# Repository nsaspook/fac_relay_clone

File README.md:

# fac_relay
Modified BLE software for the PIC24FV. Adds SPI and DFU-OTA firmware upgrades for the RN4020 module.

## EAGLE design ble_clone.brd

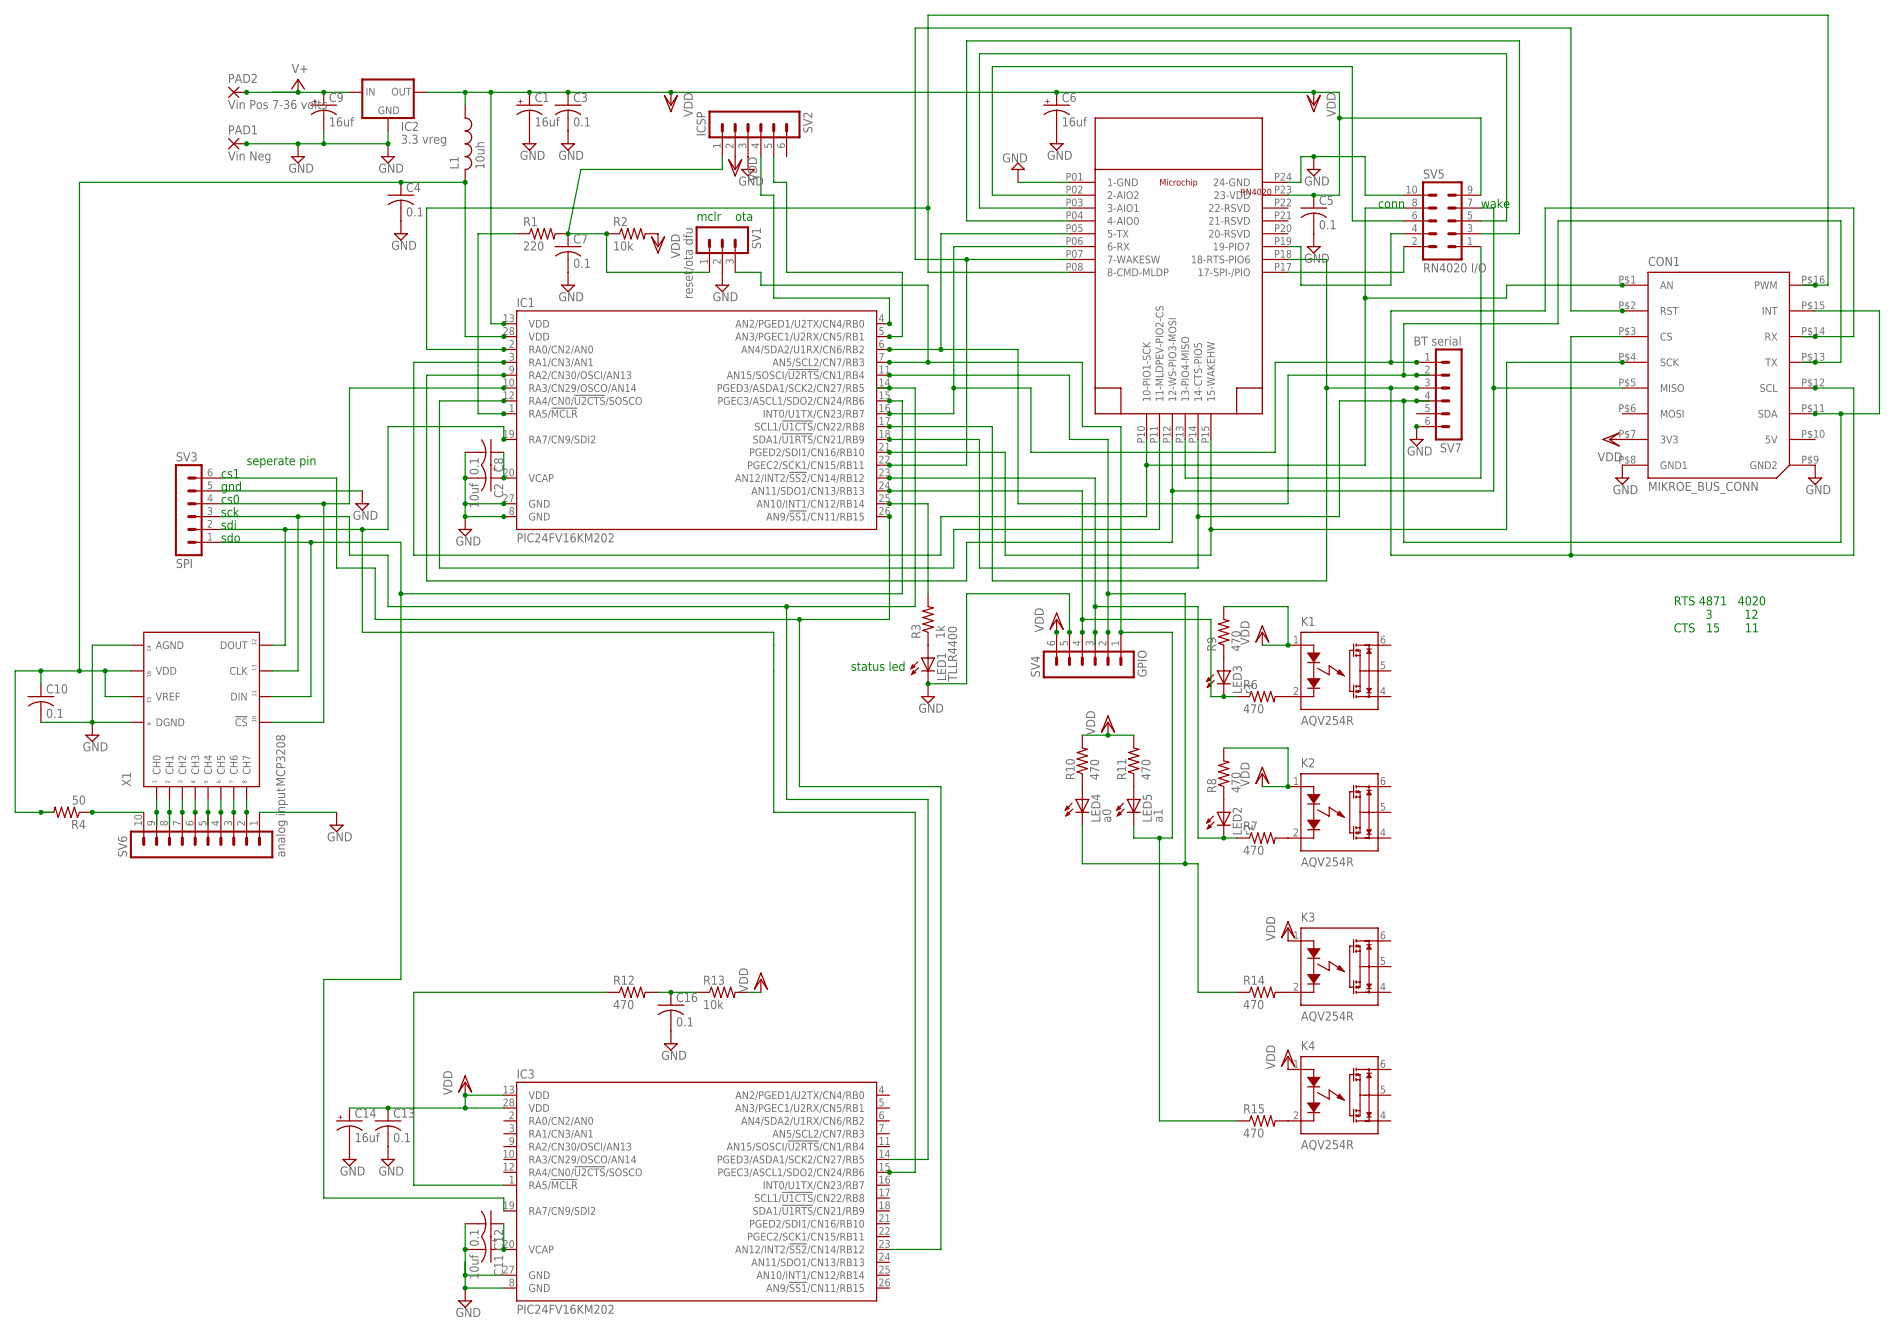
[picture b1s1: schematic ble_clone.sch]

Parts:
C1, C6, C9, C14: 16uf; TAP5-45
C2, C11: 10uf; TAP5-45
C3, C4, C5, C7, C8, C10: 0.1; C025-024X044
C12, C13, C16: 0.1; C0805
CON1: MIKROE_BUS_CONN; MIKROBUS_HOST_CONN
IC1, IC3: PIC24FV16KM202; DIL28-3
IC2: 3.3 vreg; 78XXL
K1, K2, K3, K4: AQV254R; DIL06
L1: 10uh; 0204/5
LED1: TLLR4400; LED3MM
LED2: r2; LED3MM
LED3: r1; LED3MM
LED4: a0; LED3MM
LED5: a1; LED3MM
PAD1: Vin Neg; 2,54/1,0
PAD2: Vin Pos 7-36 volts; 2,54/1,0
R1: 220; 0204V
R2, R13: 10k; 0204V
R3: 1k; 0204V
R4: 50; 0204V
R6, R7, R8, R9, R10, R11, R12, R14, R15: 470; 0204V
SV1: reset/ota dfu; MA03-1
SV2: ICSP; MA06-1
SV3: SPI; MA06-1
SV4: GPIO; MA06-1
SV5: RN4020 I/O; MA05-2
SV6: analog input; MA10-1
SV7: BT serial; MA06-1
U$1: RN4020; RN4020SMD
X1: MCP3208; DIP16

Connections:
GND: C1.-, C2.-, C3.2, C4.2, C5.2, C6.-, C7.2, C8.2, C9.-, C10.2, C11.-, C12.2, C13.2, C14.-, C16.2, CON1.P$8 (GND1), CON1.P$9 (GND2), IC1.8 (GND), IC1.27 (GND), IC2.GND, IC3.8 (GND), IC3.27 (GND), LED1.K (C), PAD1.1, SV1.2, SV2.3, SV3.5, SV4.5, SV5.10, SV6.1, SV7.6, U$1.P01 (1-GND), U$1.P24 (24-GND), X1.P$9 (DGND), X1.P$14 (AGND)
unnamed: CON1.P$16 (PWM), IC1.2 (RA0/CN2/AN0), U$1.P08 (8-CMD-MLDP)
unnamed: C7.1, R1.2, R2.1, SV1.1, SV2.1
unnamed: CON1.P$13 (TX), IC1.6 (AN4/SDA2/U1RX/CN6/RB2), SV7.2, U$1.P05 (5-TX)
unnamed: CON1.P$14 (RX), IC1.16 (INT0/U1TX/CN23/RB7), SV7.1, U$1.P06 (6-RX)
unnamed: CON1.P$2 (RST), IC1.22 (PGEC2/SCK1/CN15/RB11), U$1.P07 (7-WAKESW)
unnamed: IC1.1 (RA5/!MCLR), R1.1
unnamed: IC1.7 (AN5/SCL2/CN7/RB3), LED5.K (C), R15.1, SV1.3, SV4.1
unnamed: IC1.4 (AN2/PGED1/U2TX/CN4/RB0), SV2.4
unnamed: CON1.P$3 (CS), CON1.P$12 (SCL), IC1.17 (SCL1/!U1CTS!/CN22/RB8), SV7.3, U$1.P18 (18-RTS-PIO6)
unnamed: CON1.P$11 (SDA), CON1.P$15 (INT), IC1.18 (SDA1/!U1RTS!/CN21/RB9), SV7.4, U$1.P14 (14-CTS-PIO5)
unnamed: CON1.P$4 (SCK), IC1.21 (PGED2/SDI1/CN16/RB10), U$1.P15 (15-WAKEHW)
unnamed: CON1.P$5 (MISO), IC1.9 (RA2/CN30/OSCI/AN13), SV5.7, U$1.P12 (12-WS-PIO3-MOSI)
unnamed: CON1.P$1 (AN), IC1.3 (RA1/CN3/AN1), SV5.8, U$1.P10 (10-PIO1-SCK)
unnamed: IC1.12 (RA4/CN0/!U2CTS!/SOSCO), U$1.P11 (11-MLDPEV-PIO2-CS)
unnamed: IC1.5 (AN3/PGEC1/U2RX/CN5/RB1), SV2.5
unnamed: C4.1, C10.1, IC1.28 (VDD), L1.2, R4.2, X1.P$15 (VREF), X1.P$16 (VDD)
unnamed: C2.+, C8.1, IC1.20 (VCAP)
unnamed: IC1.10 (RA3/CN29/OSCO/AN14), SV3.4, X1.P$10 (!CS)
unnamed: IC1.19 (RA7/CN9/SDI2), IC3.15 (PGEC3/ASCL1/SDO2/CN24/RB6), SV3.2, X1.P$12 (DOUT)
unnamed: IC1.15 (PGEC3/ASCL1/SDO2/CN24/RB6), IC3.19 (RA7/CN9/SDI2), SV3.1, X1.P$11 (DIN)
unnamed: IC1.14 (PGED3/ASDA1/SCK2/CN27/RB5), IC3.14 (PGED3/ASDA1/SCK2/CN27/RB5), SV3.3, X1.P$13 (CLK)
unnamed: IC1.25 (AN10/INT1/CN12/RB14), R3.2
unnamed: IC1.26 (AN9/!SS1!/CN11/RB15), IC3.23 (AN12/INT2/!SS2!/CN14/RB12), SV3.6
unnamed: IC1.11 (AN15/SOSCI/!U2RTS!/CN1/RB4), LED4.K (C), R14.1, SV4.2
unnamed: IC1.23 (AN12/INT2/!SS2!/CN14/RB12), LED2.K (C), R7.1, SV4.3
unnamed: IC1.24 (AN11/SDO1/CN13/RB13), LED3.K (C), R6.1, SV4.4
unnamed: LED1.A, R3.1
unnamed: SV5.1, U$1.P13 (13-PIO4-MISO)
unnamed: SV5.2, U$1.P17 (17-SPI-/PIO)
unnamed: SV5.4, U$1.P19 (19-PIO7)
unnamed: SV5.3, U$1.P04 (4-AIO0)
unnamed: SV5.5, U$1.P03 (3-AIO1)
unnamed: SV5.6, U$1.P02 (2-AIO2)
unnamed: SV6.2, X1.P$8 (CH7)
unnamed: SV6.3, X1.P$7 (CH6)
unnamed: SV6.4, X1.P$6 (CH5)
unnamed: SV6.5, X1.P$5 (CH4)
unnamed: SV6.6, X1.P$4 (CH3)
unnamed: SV6.7, X1.P$3 (CH2)
unnamed: SV6.8, X1.P$2 (CH1)
unnamed: SV6.9, X1.P$1 (CH0)
unnamed: C11.+, C12.1, IC3.20 (VCAP)
unnamed: R4.1, SV6.10
unnamed: K3.2 (K), R14.2
unnamed: K1.2 (K), R6.2
unnamed: K2.2 (K), R7.2
unnamed: LED2.A, R8.1
unnamed: LED3.A, R9.1
unnamed: C16.1, R12.2, R13.1
unnamed: IC3.1 (RA5/!MCLR), R12.1
unnamed: LED4.A, R10.1
unnamed: LED5.A, R11.1
unnamed: K4.2 (K), R15.2
V+: C9.+, IC2.IN, PAD2.1
VDD: C1.+, C3.1, C5.1, C6.+, C13.1, C14.+, CON1.P$7 (3V3), IC1.13 (VDD), IC2.OUT, IC3.13 (VDD), IC3.28 (VDD), K1.1 (A), K2.1 (A), K3.1 (A), K4.1 (A), L1.1, R2.2, R8.2, R9.2, R10.2, R11.2, R13.2, SV2.2, SV4.6, SV5.9, U$1.P23 (23-VDD)

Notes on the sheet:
sdo
sdi
sck
cs0
gnd
cs1
mclr
ota
status led
conn
wake
seperate pin
RTS 4871 4020 3 12 CTS 15 11

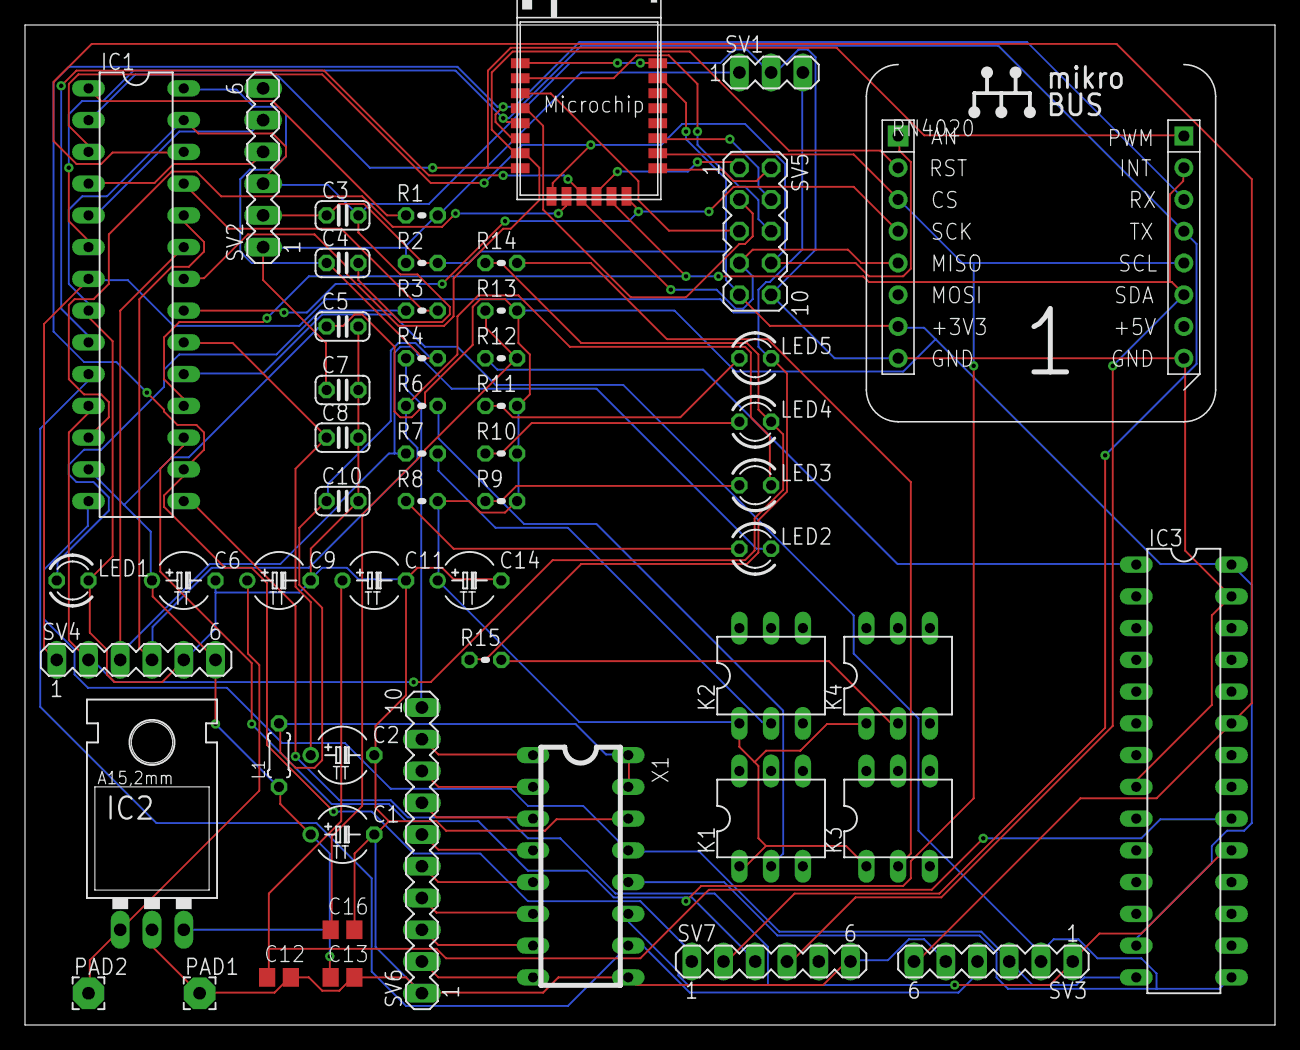
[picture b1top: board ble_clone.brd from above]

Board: 2 copper layers, 100.0 x 80.0 mm, 54 parts (0 on the bottom side), 56 nets.

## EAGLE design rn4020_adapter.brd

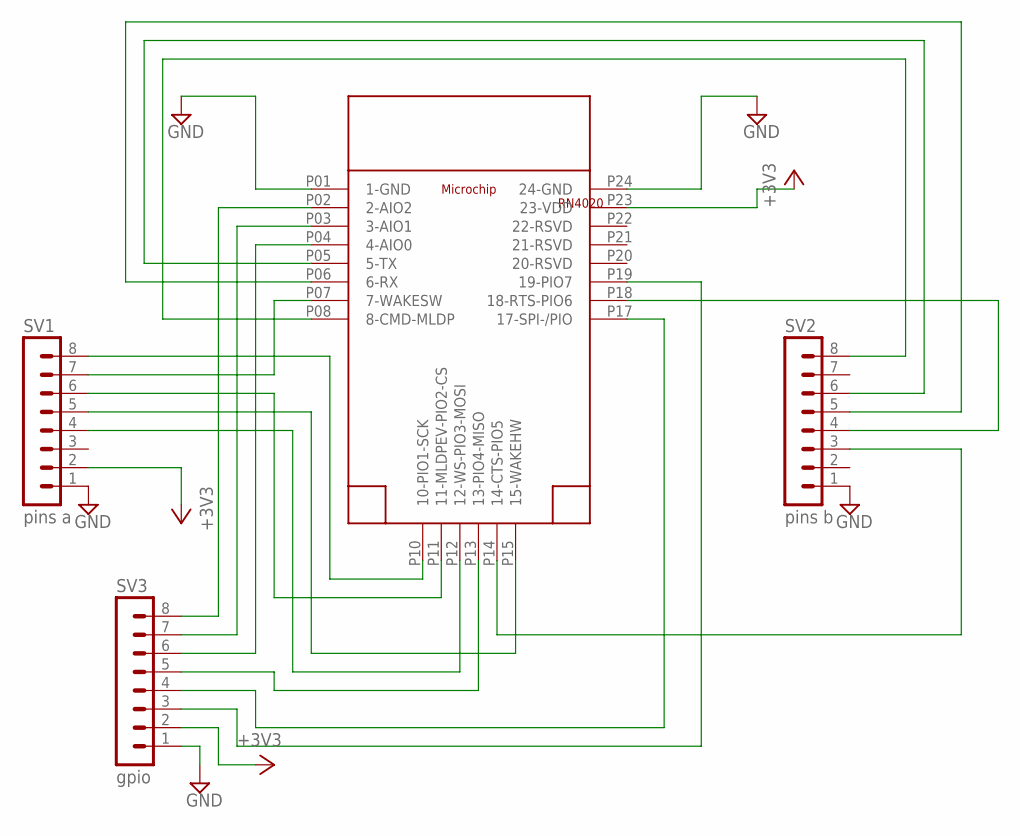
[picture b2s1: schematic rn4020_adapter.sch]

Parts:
SV1: pins a; MA08-1
SV2: pins b; MA08-1
SV3: gpio; MA08-1
U$1: RN4020; RN4020SMD

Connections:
+3V3: SV1.2, SV3.2, U$1.P23 (23-VDD)
GND: SV1.1, SV2.1, SV3.1, U$1.P01 (1-GND), U$1.P24 (24-GND)
unnamed: SV2.4, U$1.P18 (18-RTS-PIO6)
unnamed: SV2.3, U$1.P14 (14-CTS-PIO5)
unnamed: SV1.8, U$1.P10 (10-PIO1-SCK)
unnamed: SV1.7, U$1.P07 (7-WAKESW)
unnamed: SV2.8, U$1.P08 (8-CMD-MLDP)
unnamed: SV2.6, U$1.P05 (5-TX)
unnamed: SV2.5, U$1.P06 (6-RX)
unnamed: SV1.5, U$1.P15 (15-WAKEHW)
unnamed: SV1.4, U$1.P12 (12-WS-PIO3-MOSI)
unnamed: SV1.6, U$1.P11 (11-MLDPEV-PIO2-CS)
unnamed: SV3.6, U$1.P04 (4-AIO0)
unnamed: SV3.7, U$1.P03 (3-AIO1)
unnamed: SV3.8, U$1.P02 (2-AIO2)
unnamed: SV3.5, U$1.P13 (13-PIO4-MISO)
unnamed: SV3.4, U$1.P17 (17-SPI-/PIO)
unnamed: SV3.3, U$1.P19 (19-PIO7)

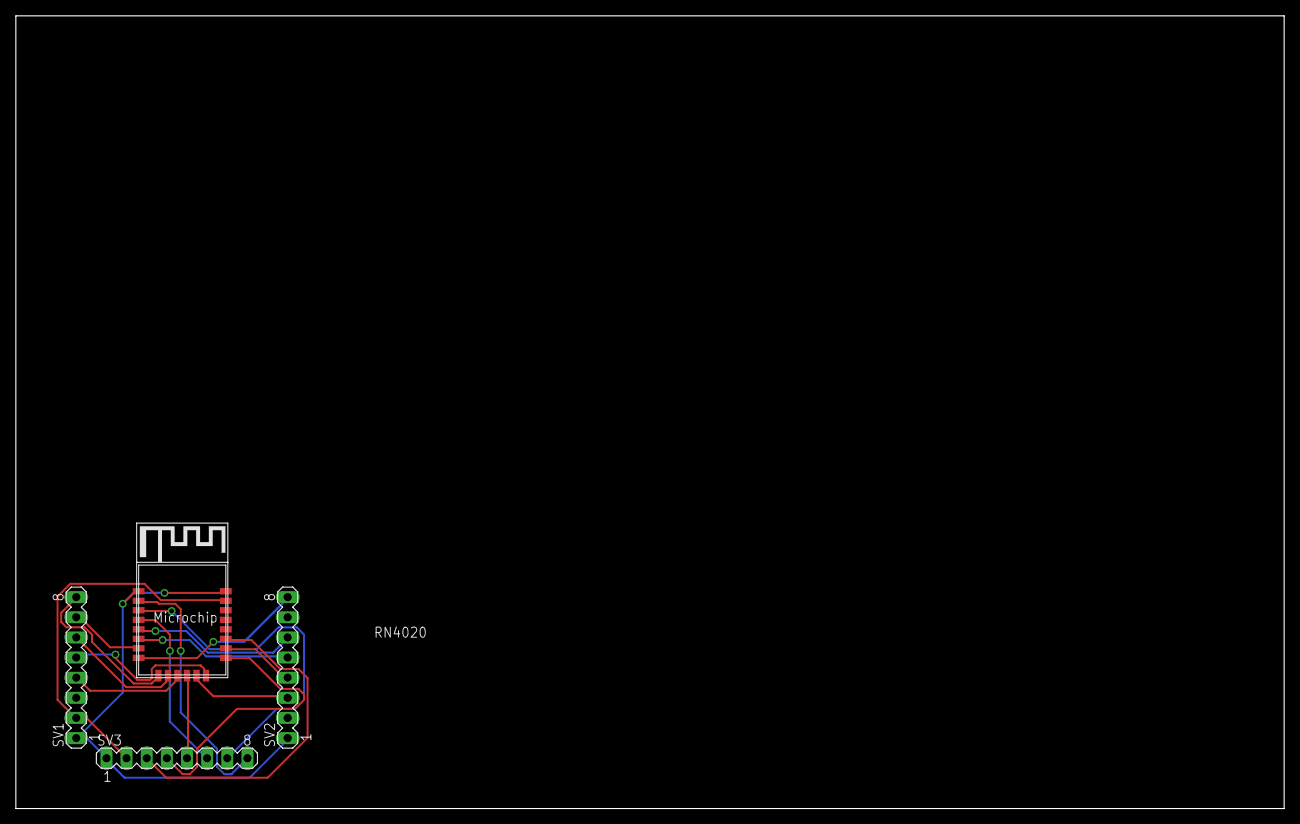
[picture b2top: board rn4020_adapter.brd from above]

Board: 2 copper layers, 160.0 x 100.0 mm, 4 parts (0 on the bottom side), 18 nets.

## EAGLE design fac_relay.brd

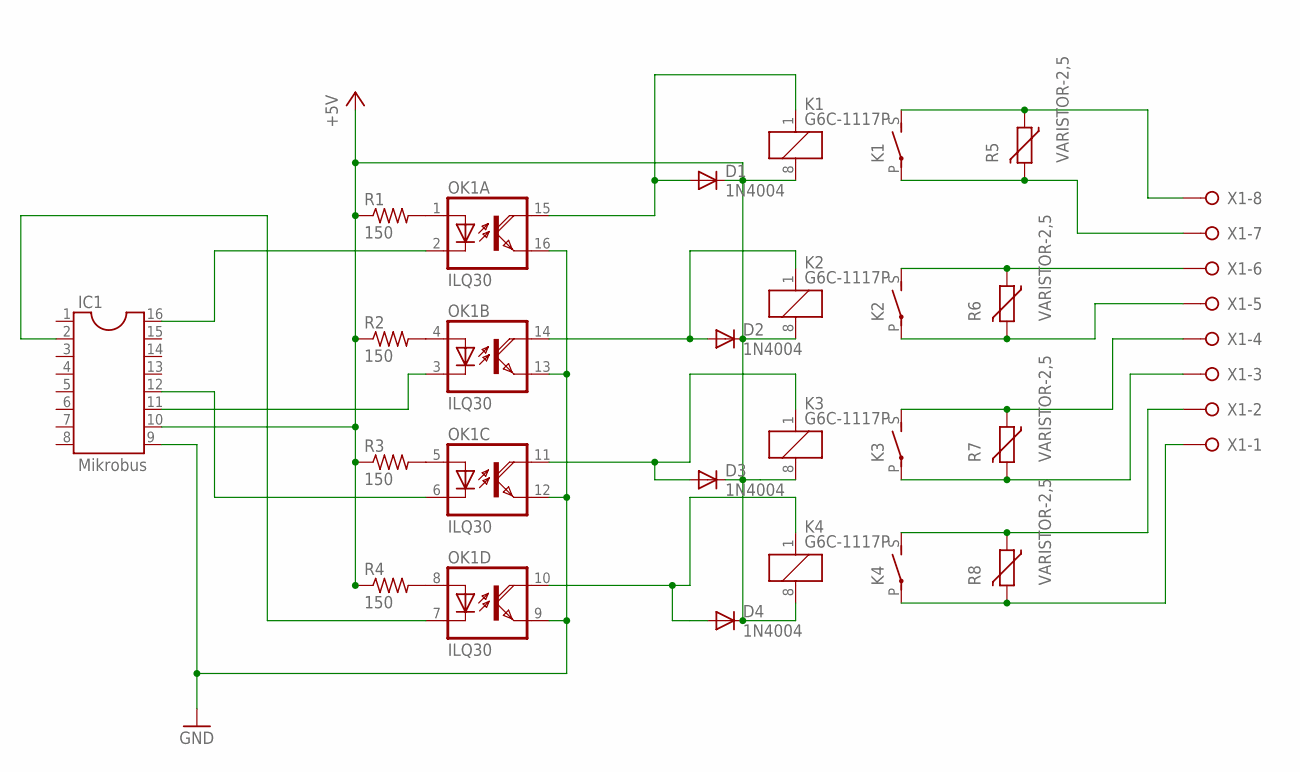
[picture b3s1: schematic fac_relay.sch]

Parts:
D1, D2, D3, D4: 1N4004; DO41-10
IC1: Mikrobus; SOCKET-16
K1, K2, K3, K4: G6C-1117P
OK1: ILQ30; DIL16
R1, R2, R3, R4: 150; 0204/5
R5, R6, R7, R8: VARISTOR-2,5; R-5
X1: W237-08P; W237-8P

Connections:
+5V: D1.C, D2.C, D3.C, D4.C, IC1.10, K1.8 (2), K2.8 (2), K3.8 (2), K4.8 (2), R1.1, R2.1, R3.1, R4.1
GND: IC1.9, OK1.9 (EMI), OK1.12 (EMI), OK1.13 (EMI), OK1.16 (EMI)
unnamed: OK1.1 (A), R1.2
unnamed: OK1.4 (A), R2.2
unnamed: OK1.5 (A), R3.2
unnamed: OK1.8 (A), R4.2
unnamed: IC1.16, OK1.2 (C)
unnamed: IC1.11, OK1.3 (C)
unnamed: IC1.12, OK1.6 (C)
unnamed: IC1.2, OK1.7 (C)
unnamed: K1.S, R5.1, X1.8
unnamed: K1.P, R5.2, X1.7
unnamed: D1.A, K1.1, OK1.15 (COL)
unnamed: D2.A, K2.1, OK1.14 (COL)
unnamed: D3.A, K3.1, OK1.11 (COL)
unnamed: D4.A, K4.1, OK1.10 (COL)
unnamed: K2.S, R6.1, X1.6
unnamed: K2.P, R6.2, X1.5
unnamed: K3.S, R7.1, X1.4
unnamed: K3.P, R7.2, X1.3
unnamed: K4.S, R8.1, X1.2
unnamed: K4.P, R8.2, X1.1

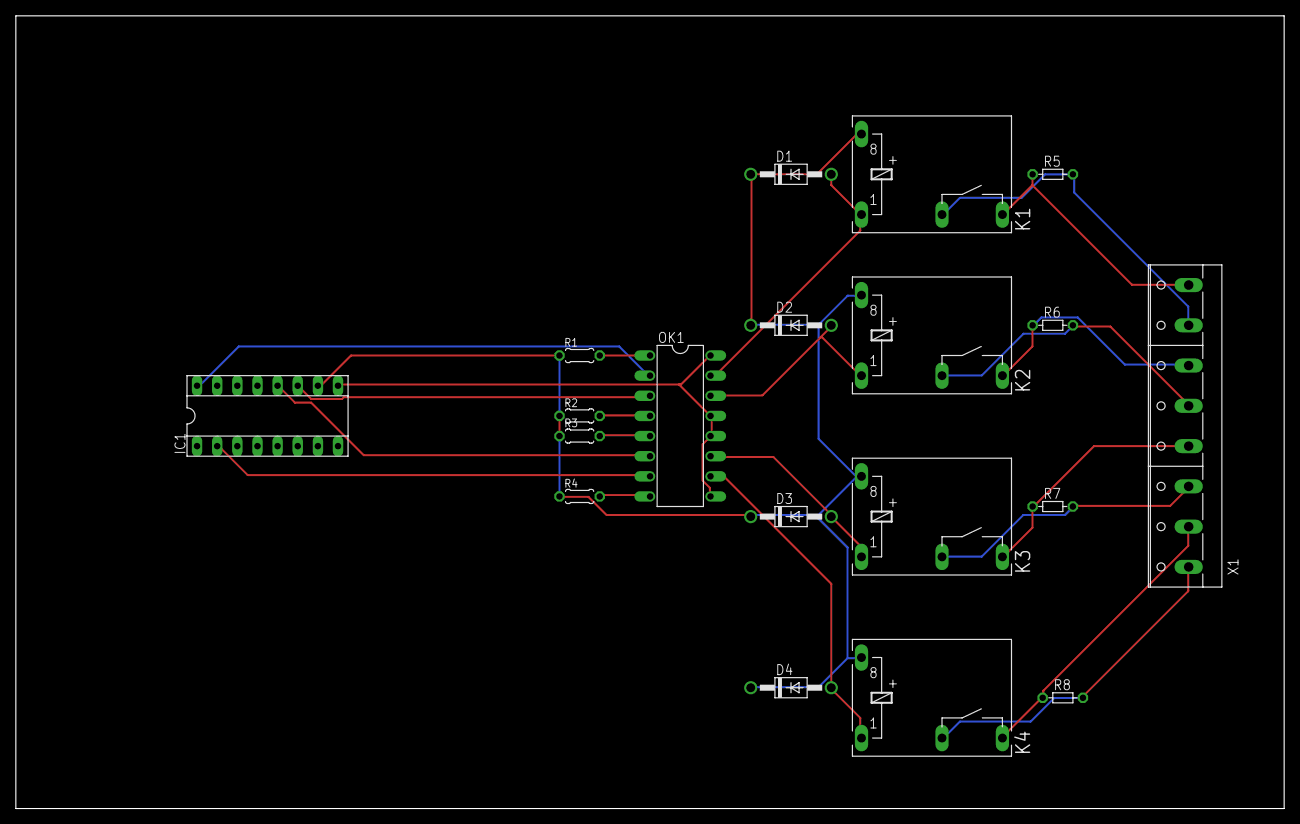
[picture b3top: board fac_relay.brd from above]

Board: 2 copper layers, 160.0 x 100.0 mm, 19 parts (0 on the bottom side), 22 nets.

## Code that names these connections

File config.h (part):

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#define FCY (16000000)                              //8MHz FRC, 4XPLL, /2 for Fcy

//RN4020 BTLE
#define BT_OTA_UPD	PORTBbits.RB3
#define BT_OTA_UPD_TRIS	TRISBbits.TRISB3

#define BT_WAKE_HW      LATBbits.LATB10                       //Hardware wake from dormant state; BT_WAKE_HW
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#define BT_CMD      LATAbits.LATA0                 //Place RN4020 module in command mode, low for MLDP mode
#define BT_CMD_TRIS TRISAbits.TRISA0

#define BT_CONNECTED        PORTAbits.RA1                     //RN4020 module is connected to central device
#define BT_CONNECTED_TRIS   TRISAbits.TRISA1

#define BT_WS       PORTAbits.RA2                         //RN4020 module is awake and active
#define BT_WS_TRIS  TRISAbits.TRISA2

#define BT_MLDP_EV      PORTAbits.RA4                         //RN4020 module in MLDP mode has a pending event
#define BT_MLDP_EV_TRIS TRISAbits.TRISA4

//UART
#define U1CTS_TRIS      TRISBbits.TRISB8
#define U1CTS_PORT	PORTBbits.RB8
#define U1CTS_RP_NUM    23

#define U1RTS_TRIS      TRISBbits.TRISB9
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#define U1RTS_RP_REG    RPOR6bits.RP12R

#define U1RX_TRIS   TRISBbits.TRISB2  //BT_RX
#define U1RX_PORT   PORTBbits.RB2
#define U1RX_RP_NUM 24

#define U1TX_TRIS   TRISBbits.TRISB7  //BT_TX
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
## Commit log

2016-11-03 spi adc working
2016-11-04 spi updates
2016-11-08 updat
2016-11-17 add slave code
2016-11-21 link code
2018-09-01 update OTA update code, not tested
2018-09-01 refactor OTA update code, not tested
2018-09-01 update code

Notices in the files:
config.h:
Copyright (C) 2014 Microchip Technology Inc. and its subsidiaries.  You may use this software and any derivatives
Copyright 2015-2016 Espressif Systems (Shanghai) PTE LTD
Licensed under the Apache License, Version 2.0 (the "License");
